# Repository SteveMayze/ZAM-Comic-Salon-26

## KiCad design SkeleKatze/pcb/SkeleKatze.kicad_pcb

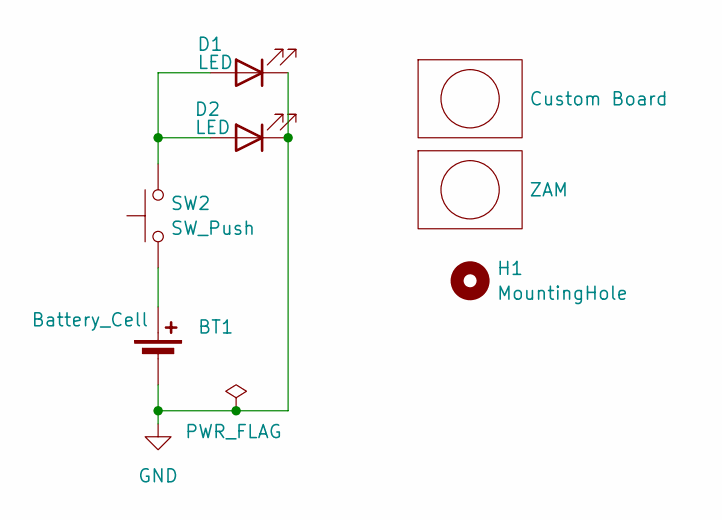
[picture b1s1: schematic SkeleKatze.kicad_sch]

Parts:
BT1: Battery_Cell; CR1220_Halter
D1, D2: LED; LED D5.0mm SMD
H1: MountingHole; MountingHole_2.7mm_M2.5
Lg1: Custom Board; SkeleKatze-R2.0
Lg2: ZAM; ZAM_LOGO_440
SW2: SW_Push; SW_PUSH_SPST_ 1208Yd

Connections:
GND: BT1.2 (-), D1.1 (K), D2.1 (K)
unnamed: BT1.1 (+), SW2.1
unnamed: D1.2 (A), D2.2 (A), SW2.2

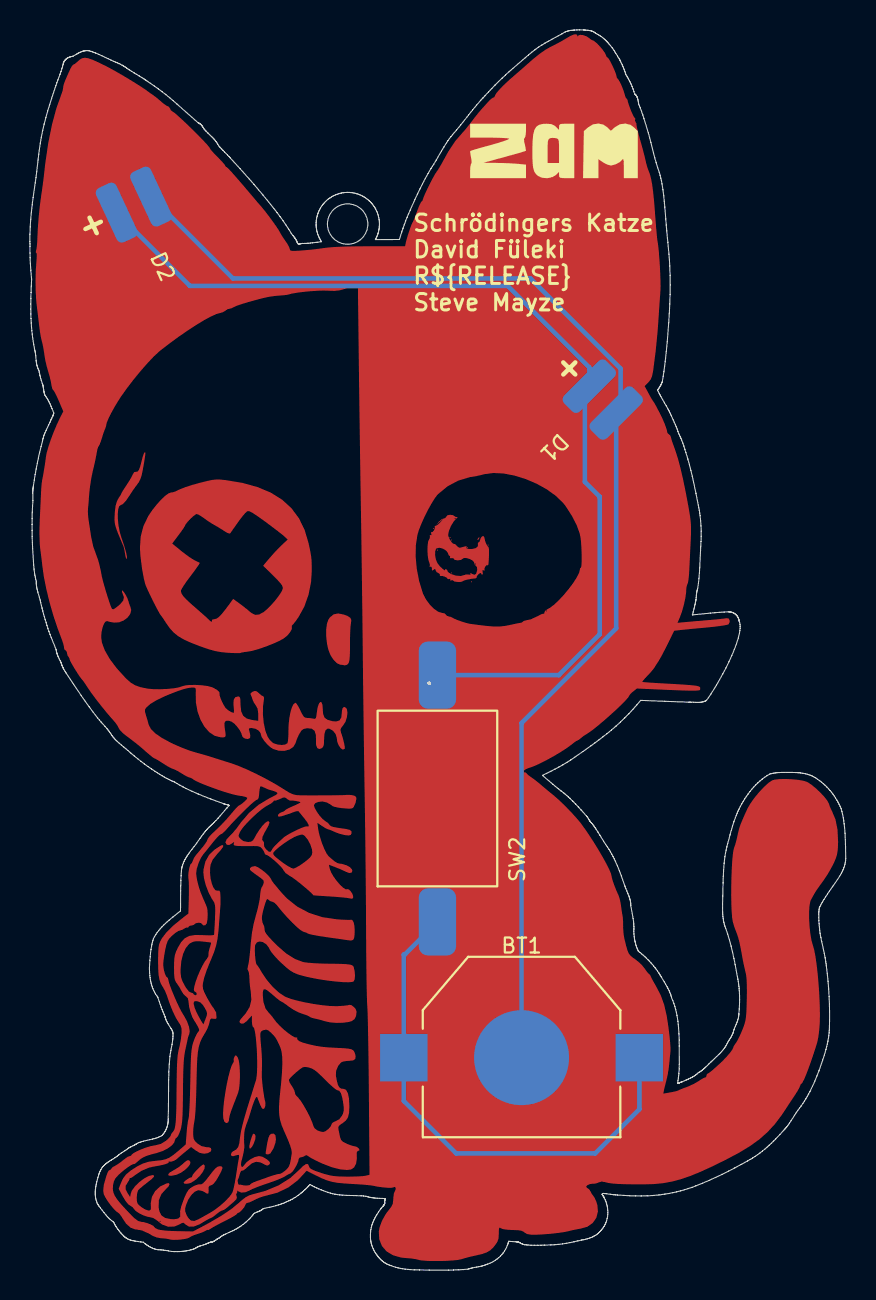
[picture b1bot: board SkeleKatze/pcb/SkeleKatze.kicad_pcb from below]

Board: 2 copper layers, 54.5 x 82.9 mm, 7 parts (5 on the bottom side), 3 nets.

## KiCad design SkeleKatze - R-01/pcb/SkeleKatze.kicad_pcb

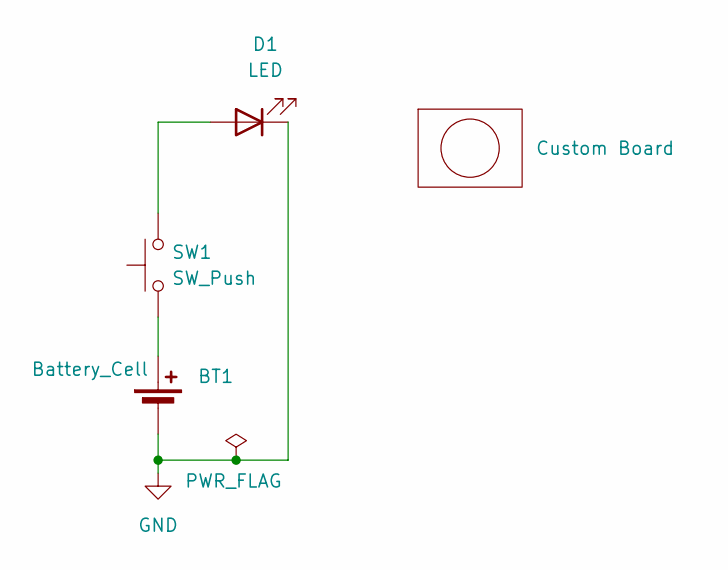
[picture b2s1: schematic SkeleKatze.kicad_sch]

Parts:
BT1: Battery_Cell; CR1220_Halter
D1: LED; LED D5.0mm SMD
Lg1: Custom Board; SkeleKatze-Combined
SW1: SW_Push; SW_PUSH_SPST_ 1208Yd

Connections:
GND: BT1.2 (-), D1.1 (K)
unnamed: BT1.1 (+), SW1.1
unnamed: D1.2 (A), SW1.2

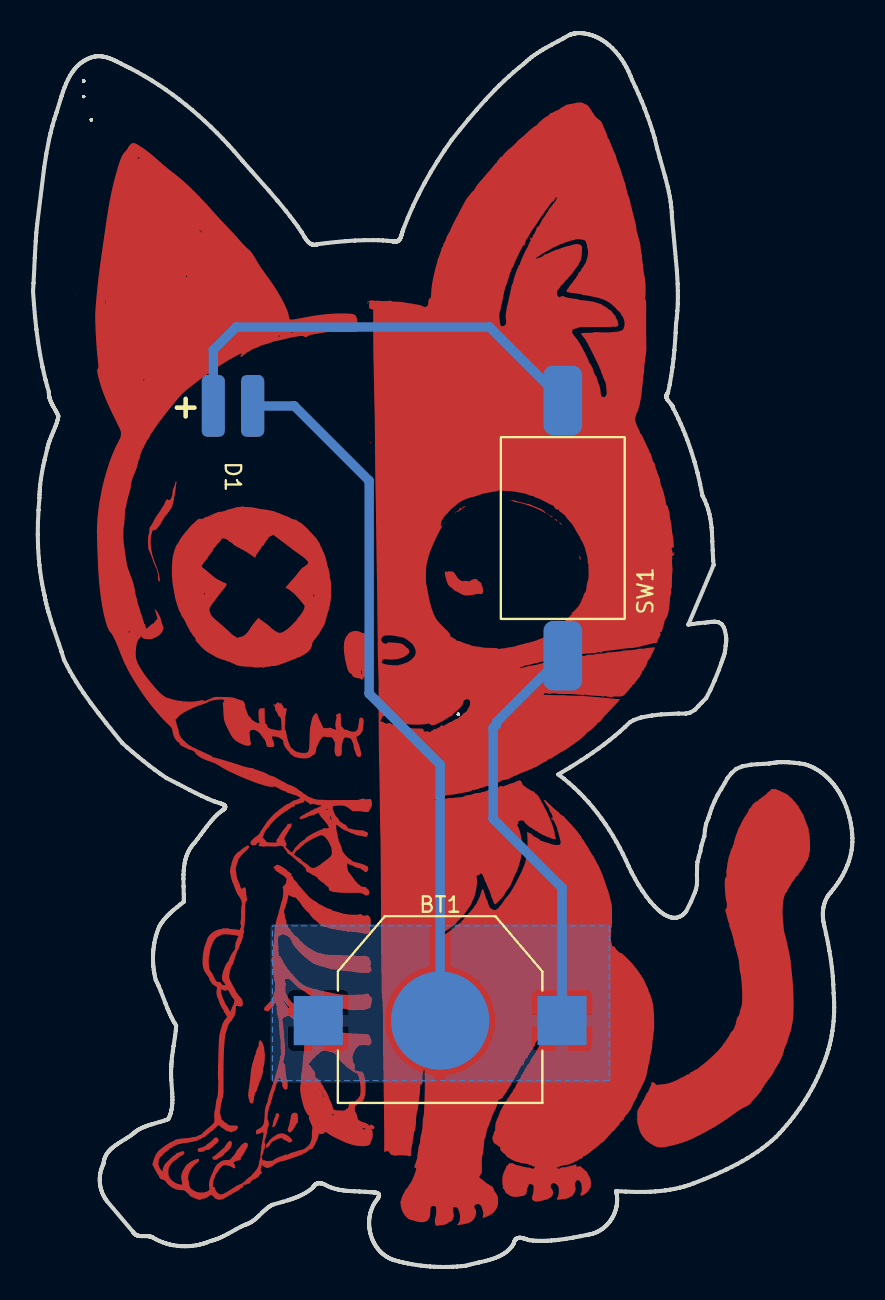
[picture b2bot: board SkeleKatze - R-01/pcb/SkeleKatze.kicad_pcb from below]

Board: 2 copper layers, 52.9 x 79.7 mm, 4 parts (3 on the bottom side), 3 nets.

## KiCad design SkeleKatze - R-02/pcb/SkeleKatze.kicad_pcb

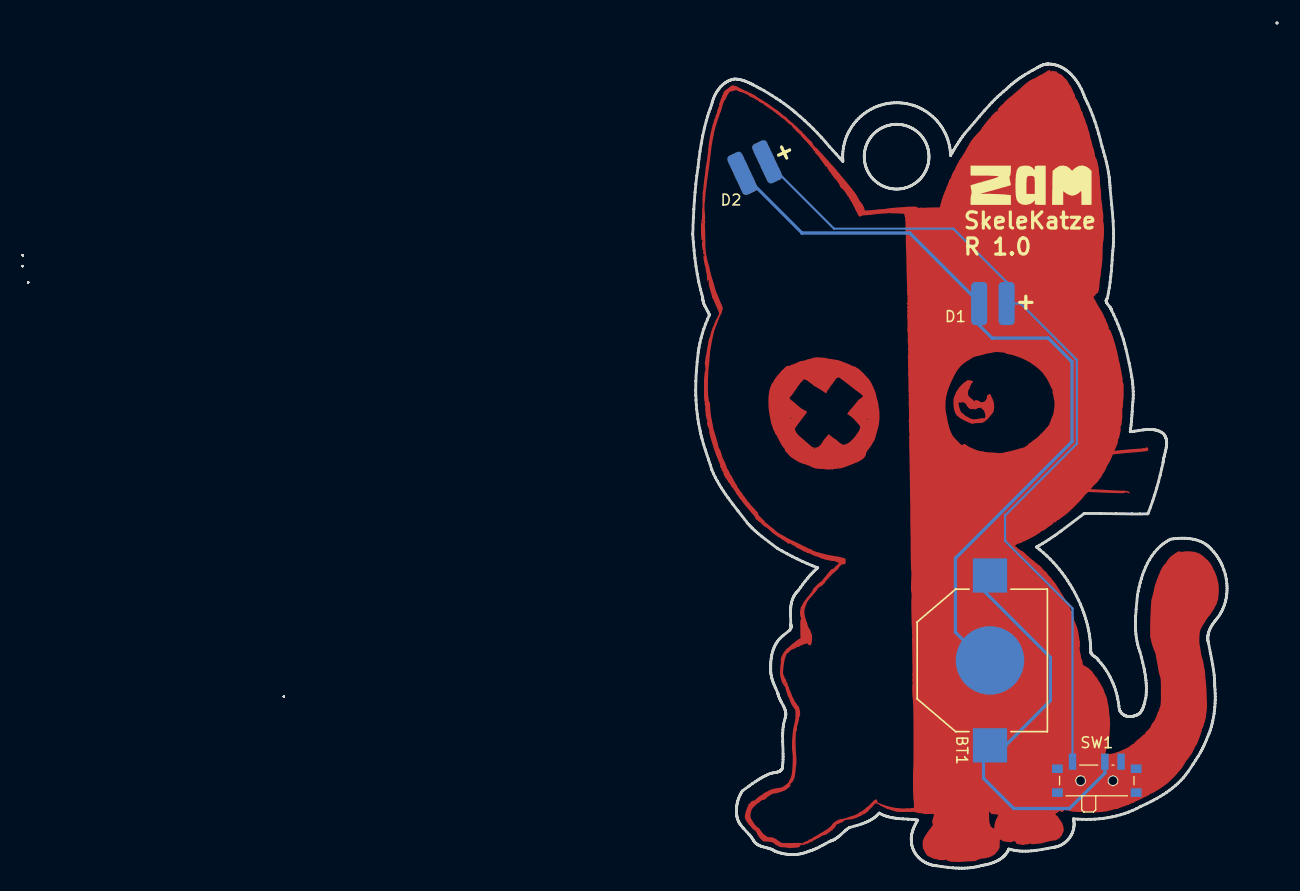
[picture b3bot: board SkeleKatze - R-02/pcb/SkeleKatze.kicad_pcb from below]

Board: 2 copper layers, 49.5 x 74.5 mm, 6 parts (5 on the bottom side), 3 nets.

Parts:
BT1: Battery_Cell; CR1220_Halter
D1, D2: LED; LED D5.0mm SMD
Lg1: Custom Board; SkeleKatze-Combined
Lg2: ZAM; ZAM_LOGO_440
SW1: SW_SPDT; SW_SPDT_PCM12

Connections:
GND: BT1.2 (-), D1.1 (K), D2.1 (K)
unnamed: BT1.1 (+), SW1.2 (B)
unnamed: D1.2 (A), D2.2 (A), SW1.1 (A)

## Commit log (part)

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2026-04-24 Ignore practice trial directories
2026-04-24 upated
2026-04-26 Stop tracking .history
2026-04-26 Update GIT ignore
2026-04-29 Stop tracking generated gerber files
2026-04-29 Stop tracking generated gerber zip
2026-04-29 rerouted tracks to LED2
2026-05-06 Back up R-02 before working on the final design
2026-05-07 Final cut R 1.0
2026-05-07 Adds .vscode to the .gitignore for local settings
2026-05-07 Creates a Non-Front-Silkscreen version
2026-05-12 Generated final artefacts
2026-05-12 Removes the first cut files
2026-05-12 Created an archive for Kicad R 10.0
2026-05-17 Corrects the F.Mask to cover _all_ where the UV image is to be printed
